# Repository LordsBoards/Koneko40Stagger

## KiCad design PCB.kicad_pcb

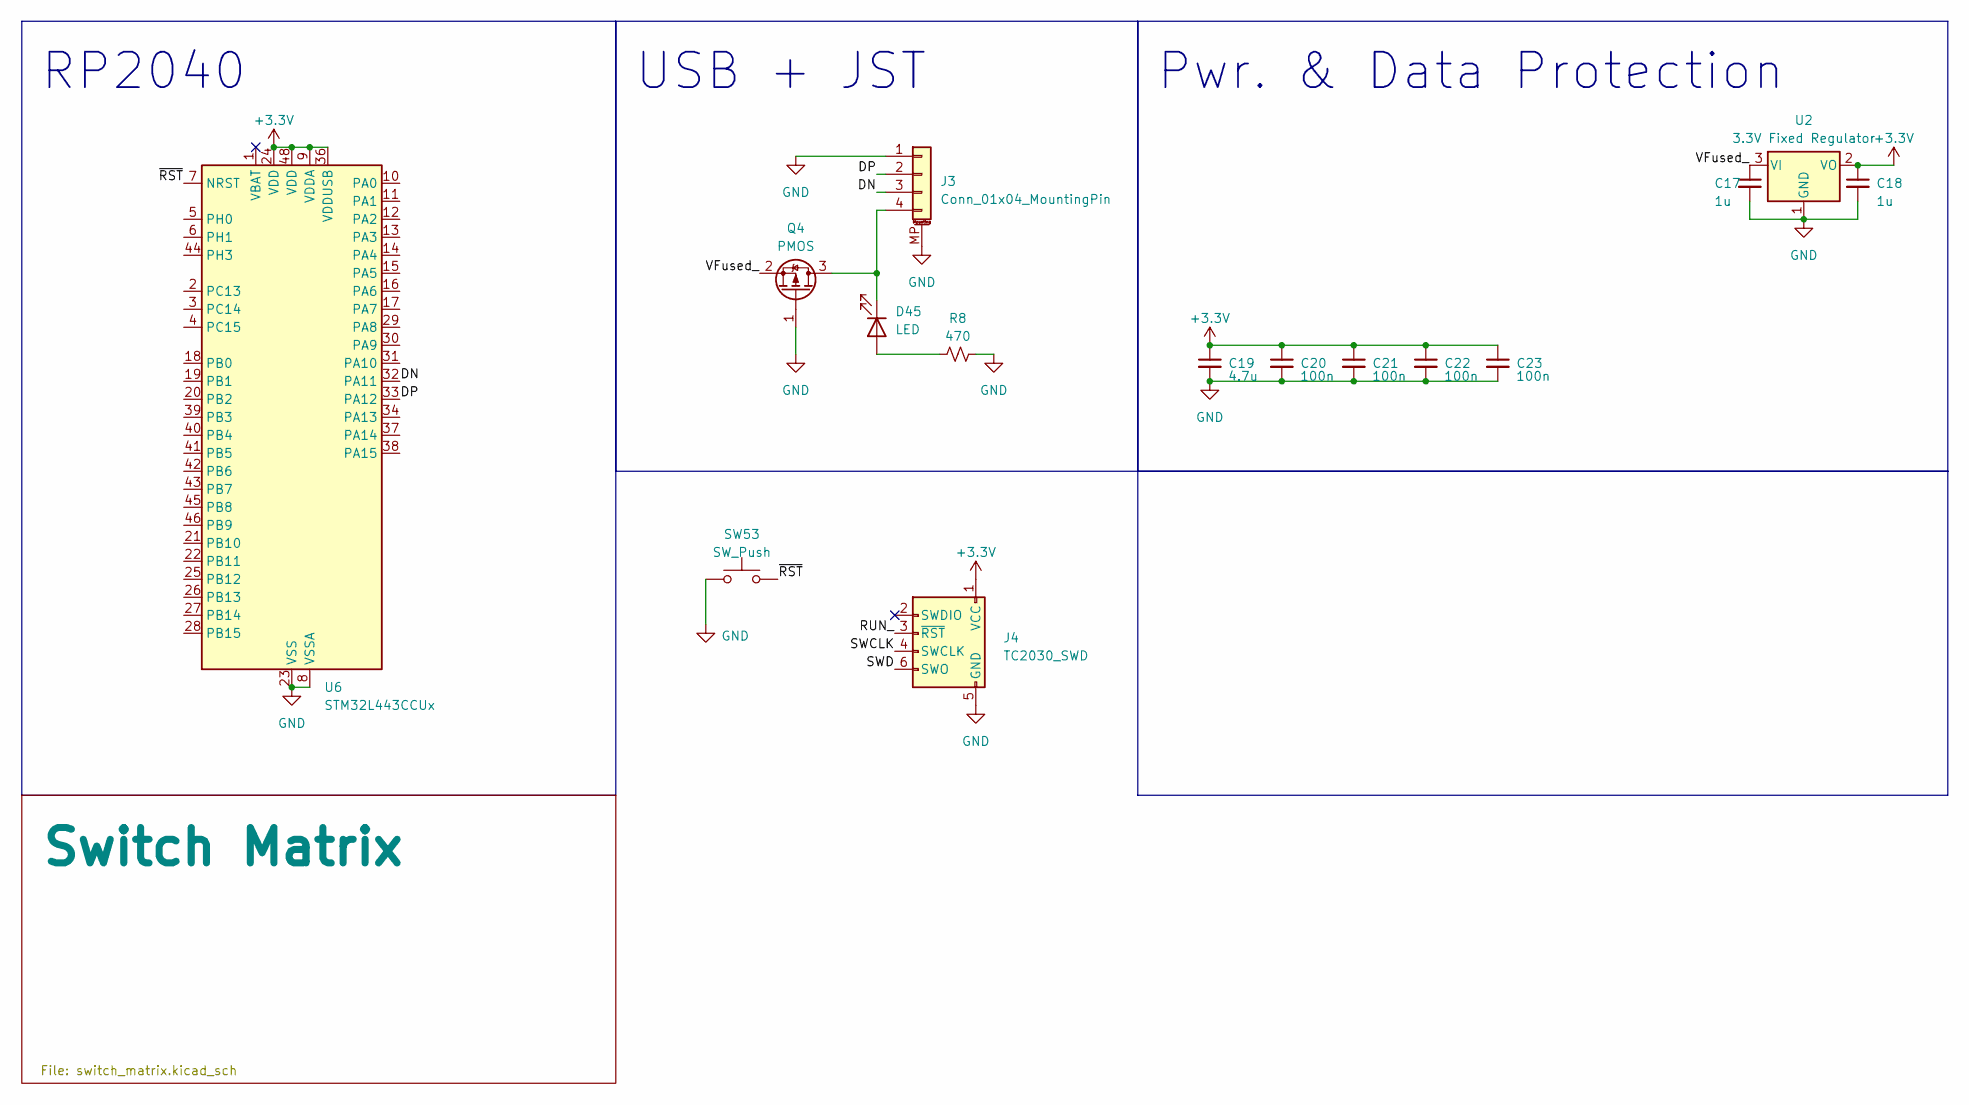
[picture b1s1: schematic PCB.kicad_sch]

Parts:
C17, C18: 1u; C_0402_1005Metric; LCSC C52923
C19: 4.7u; C_0402_1005Metric; LCSC C52923
C20, C21, C22, C23: 100n; C_0402_1005Metric; LCSC C1525
D45: LED; R_0603_1608Metric; LCSC C2286
J3: Conn_01x04_MountingPin; Molex_Pico-EZmate_78171-0004_1x04-1MP_P1.20mm_Vertical; LCSC C528030
J4: TC2030_SWD; CON_TC2030_outlined
Q4: PMOS; SOT-323_SC-70; LCSC C99272
R8: 470; R_0603_1608Metric; LCSC C23179
SW53: SW_Push; SW_SPST_SKQG_WithoutStem; LCSC C115351
U2: 3.3V Fixed Regulator; TSOT-23; LCSC C150715
U6: STM32L443CCUx; QFN-48-1EP_7x7mm_P0.5mm_EP5.6x5.6mm

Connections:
+3.3V: C18.1, C19.1, C20.1, C21.1, C22.1, C23.1, J4.1 (VCC), U2.2 (VO), U6.9 (VDDA), U6.24 (VDD), U6.36 (VDDUSB), U6.48 (VDD); also elsewhere on the board
/DN: J3.3, U6.32 (PA11); also elsewhere on the board
/DP: J3.2, U6.33 (PA12); also elsewhere on the board
/RUN_: J4.3 (~RST)
/SWCLK: J4.4 (SWCLK)
/SWD: J4.6 (SWO)
/VFused_: C17.1, Q4.2 (S), U2.3 (VI)
/~RST: SW53.2, U6.7 (NRST)
GND: C17.2, C18.2, C19.2, C20.2, C21.2, C22.2, C23.2, J3.1, J3.MP (MountPin), J4.5 (GND), Q4.1 (G), R8.1, SW53.1, U2.1 (GND), U6.8 (VSSA), U6.23 (VSS), U6.35 (VSS), U6.47 (VSS), U6.49 (VSS); also elsewhere on the board
unnamed: D45.2 (A), R8.2
unnamed 69: D45.1 (K), J3.4, Q4.3 (D); also elsewhere on the board

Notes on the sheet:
USB + JST
RP2040
Pwr. & Data Protection

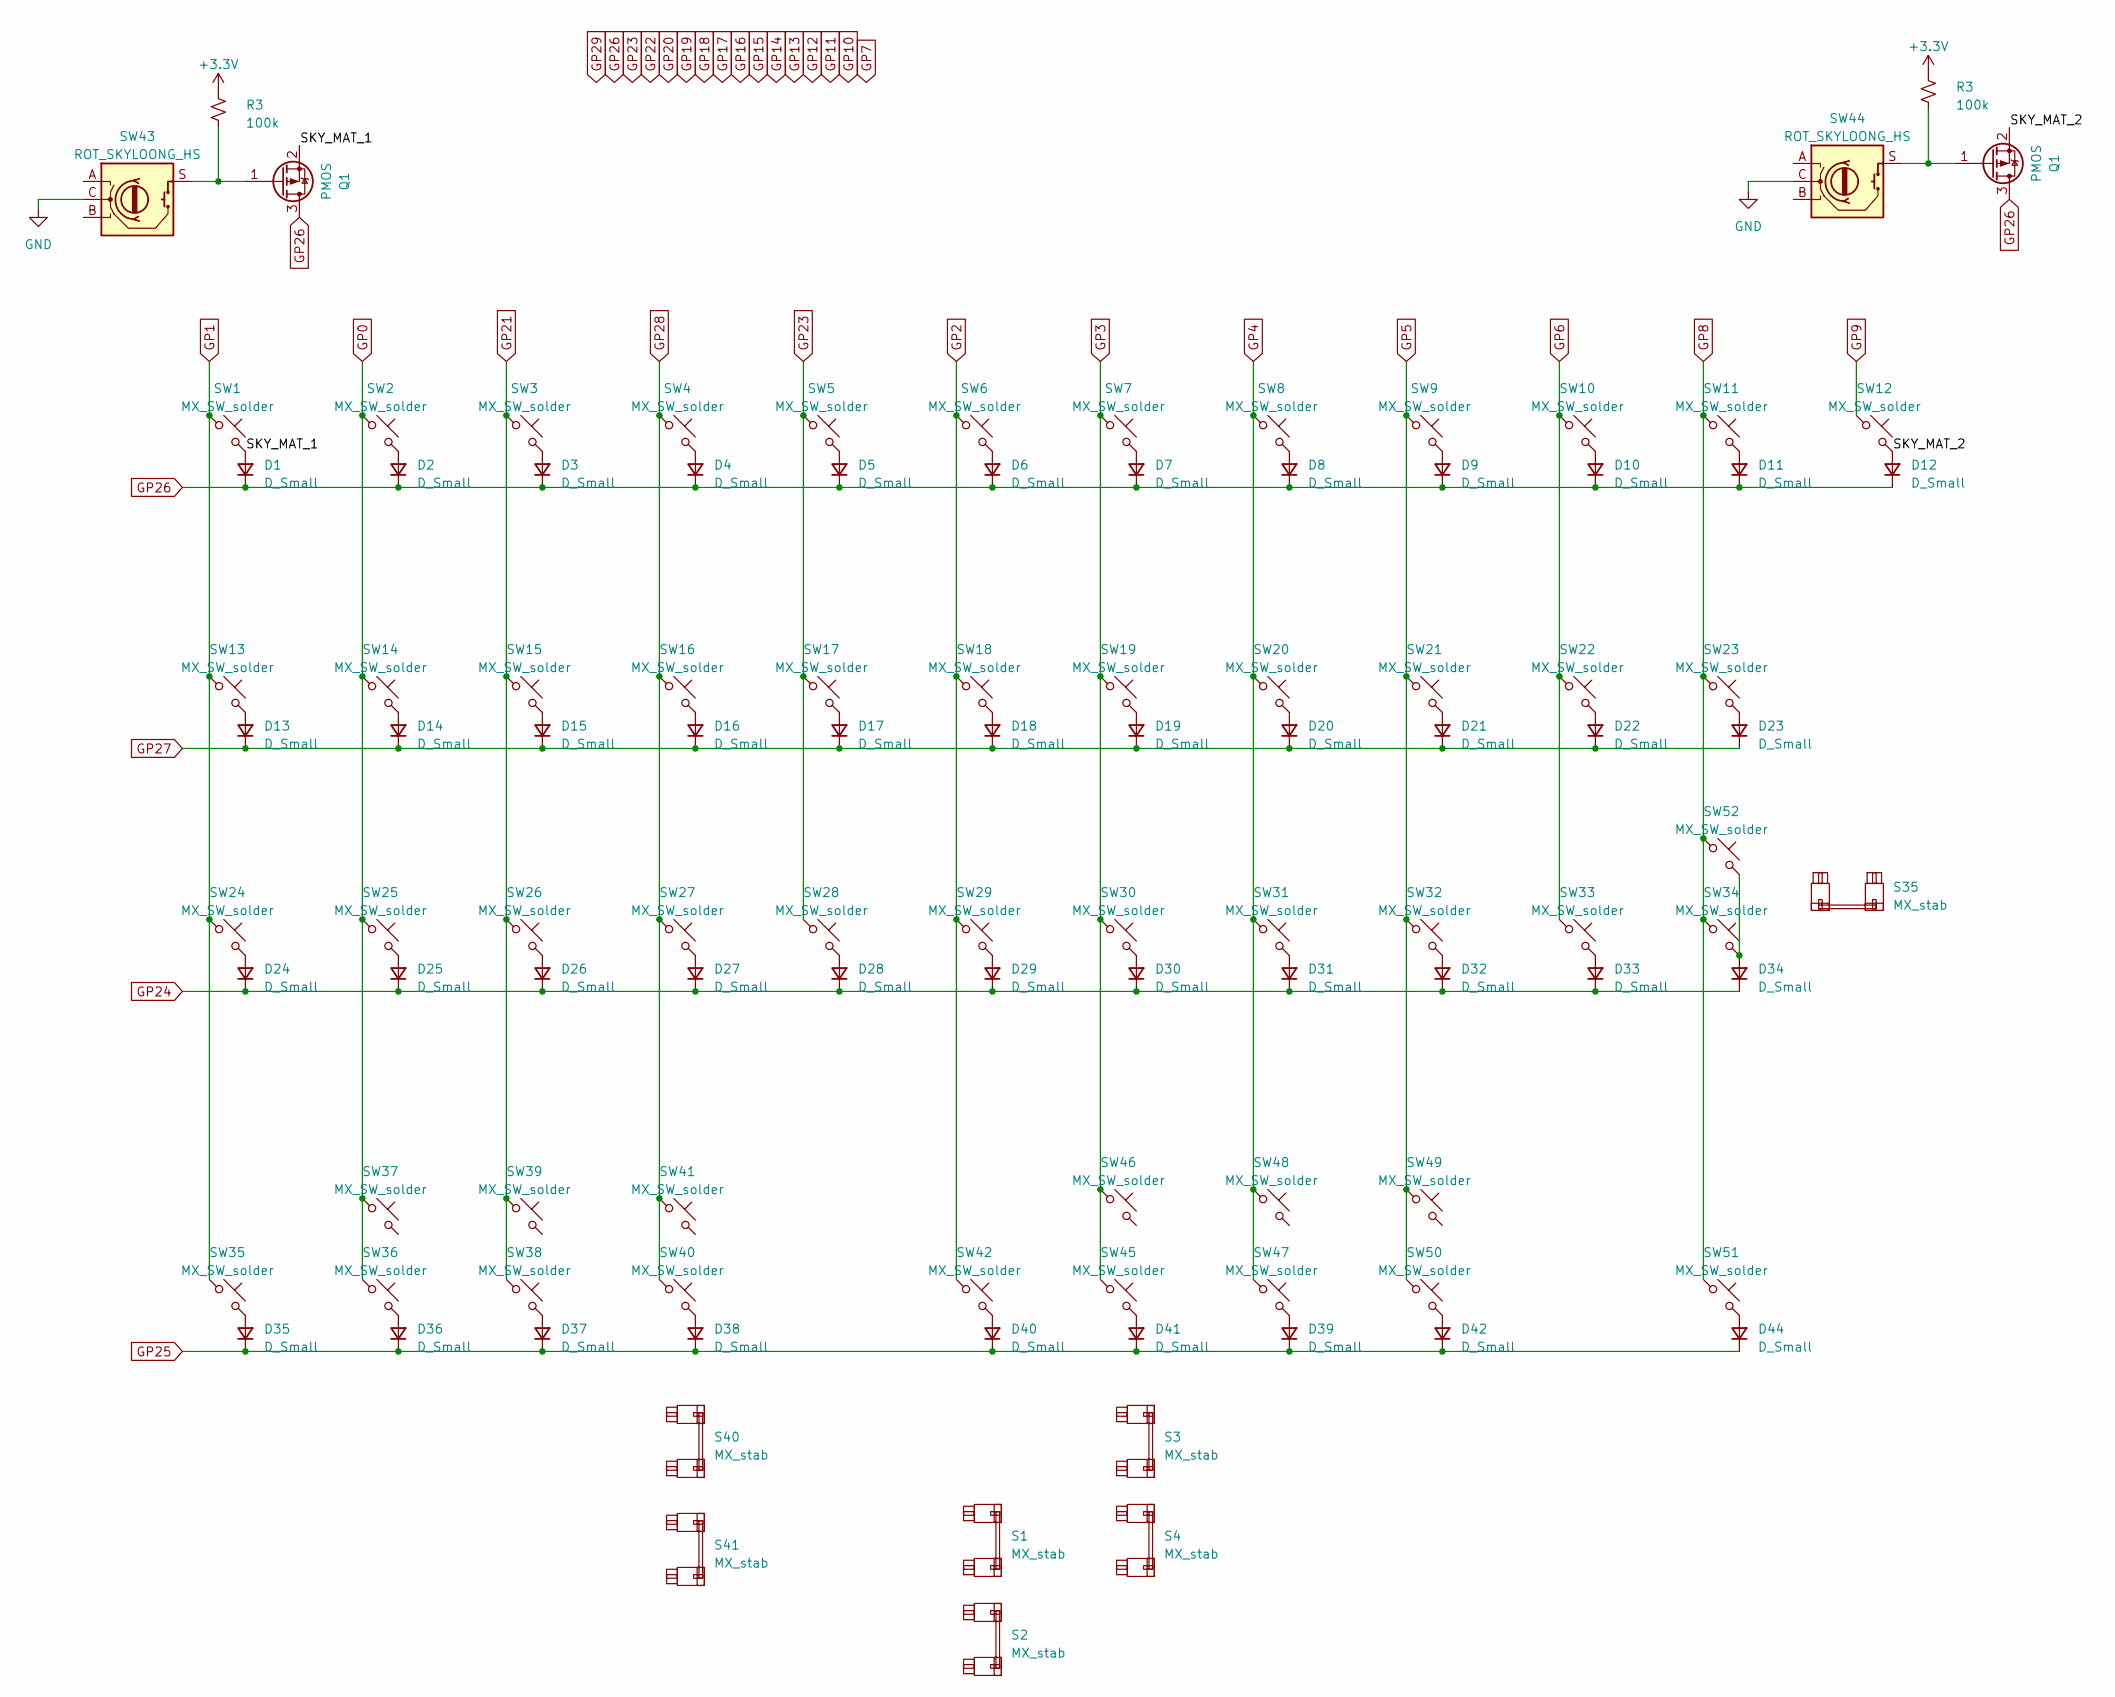
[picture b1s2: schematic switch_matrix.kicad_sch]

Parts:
D1, D2, D3, D4, D5, D6, D7, D8, D9, D10, D11, D12, D13, D14, D15, D16, D17, D18, D19, D20, D21, D22, D23, D24, D25, D26, D27, D28, D29, D30, D31, D32, D33, D34, D35, D36, D37, D38, D39, D40, D41, D42, D44: D_Small; D_SOD-123; LCSC C81598
Q1: PMOS; SOT-323_SC-70; LCSC C99272
R3: 100k; R_0402_1005Metric; LCSC C106234
S1: MX_stab; STAB_MX_P_7u
S2: MX_stab; STAB_MX_P_10u
S3, S40: MX_stab; STAB_MX_P_3u
S4, S35: MX_stab; STAB_MX_P_2.25u
S41: MX_stab; STAB_MX_P_2.75u
SW1, SW2, SW3, SW4, SW5, SW6, SW7, SW8, SW9, SW10, SW11, SW12, SW14, SW15, SW16, SW17, SW18, SW19, SW20, SW21, SW22, SW25, SW26, SW27, SW28, SW29, SW30, SW31, SW32, SW33, SW35, SW36, SW38, SW39, SW40, SW41, SW42, SW45, SW46, SW47, SW48, SW50, SW51, SW52: MX_SW_solder; SW_MX_1u
SW13, SW34: MX_SW_solder; SW_MX_1.25u
SW23, SW24: MX_SW_solder; SW_MX_1.75u
SW37, SW49: MX_SW_solder; SW_MX_1.5u
SW43, SW44: ROT_SKYLOONG_HS; ROT_SKYLOONG_HS-Switch

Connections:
/Switch Matrix/SKY_MAT_1: D1.2 (A), SW1.2; also elsewhere on the board
/Switch Matrix/SKY_MAT_2: D12.2 (A), SW12.2; also elsewhere on the board
GND: SW43.C, SW44.C; also elsewhere on the board
GP0: SW2.1, SW14.1, SW25.1, SW36.1, SW37.1
GP1: SW1.1, SW13.1, SW24.1, SW35.1
GP2: SW6.1, SW18.1, SW29.1, SW42.1
GP3: SW7.1, SW19.1, SW30.1, SW45.1, SW46.1
GP4: SW8.1, SW20.1, SW31.1, SW47.1, SW48.1
GP5: SW9.1, SW21.1, SW32.1, SW49.1, SW50.1
GP6: SW10.1, SW22.1, SW33.1
GP8: SW11.1, SW23.1, SW34.1, SW51.1, SW52.1
GP9: SW12.1
GP21: SW3.1, SW15.1, SW26.1, SW38.1, SW39.1
GP23: SW5.1, SW17.1, SW28.1
GP24: D24.1 (K), D25.1 (K), D26.1 (K), D27.1 (K), D28.1 (K), D29.1 (K), D30.1 (K), D31.1 (K), D32.1 (K), D33.1 (K), D34.1 (K)
GP25: D35.1 (K), D36.1 (K), D37.1 (K), D38.1 (K), D39.1 (K), D40.1 (K), D41.1 (K), D42.1 (K), D44.1 (K)
GP26: D1.1 (K), D2.1 (K), D3.1 (K), D4.1 (K), D5.1 (K), D6.1 (K), D7.1 (K), D8.1 (K), D9.1 (K), D10.1 (K), D11.1 (K), D12.1 (K); also elsewhere on the board
GP27: D13.1 (K), D14.1 (K), D15.1 (K), D16.1 (K), D17.1 (K), D18.1 (K), D19.1 (K), D20.1 (K), D21.1 (K), D22.1 (K), D23.1 (K)
GP28: SW4.1, SW16.1, SW27.1, SW40.1, SW41.1
unnamed: D2.2 (A), SW2.2
unnamed: D3.2 (A), SW3.2
unnamed: D4.2 (A), SW4.2
unnamed: D5.2 (A), SW5.2
unnamed: D6.2 (A), SW6.2
unnamed: D7.2 (A), SW7.2
unnamed: D8.2 (A), SW8.2
unnamed: D9.2 (A), SW9.2
unnamed: D10.2 (A), SW10.2
unnamed: D11.2 (A), SW11.2
unnamed: D13.2 (A), SW13.2
unnamed: D14.2 (A), SW14.2
unnamed: D15.2 (A), SW15.2
unnamed: D16.2 (A), SW16.2
unnamed: D17.2 (A), SW17.2
unnamed: D18.2 (A), SW18.2
unnamed: D19.2 (A), SW19.2
unnamed: D20.2 (A), SW20.2
unnamed: D21.2 (A), SW21.2
unnamed: D22.2 (A), SW22.2
unnamed: D23.2 (A), SW23.2
unnamed: D24.2 (A), SW24.2
unnamed: D25.2 (A), SW25.2
unnamed: D26.2 (A), SW26.2
unnamed: D27.2 (A), SW27.2
unnamed: D28.2 (A), SW28.2
unnamed: D29.2 (A), SW29.2
unnamed: D30.2 (A), SW30.2
unnamed: D31.2 (A), SW31.2
unnamed: D32.2 (A), SW32.2
unnamed: D33.2 (A), SW33.2
unnamed: D34.2 (A), SW34.2, SW52.2
unnamed: D35.2 (A), SW35.2
unnamed: D36.2 (A), SW36.2
unnamed: D37.2 (A), SW38.2
unnamed: D38.2 (A), SW40.2
unnamed: D39.2 (A), SW47.2
unnamed: D40.2 (A), SW42.2
unnamed: D41.2 (A), SW45.2
unnamed: D42.2 (A), SW50.2
unnamed: D44.2 (A), SW51.2
unnamed 70: SW44.S; also elsewhere on the board
unnamed 71: SW43.S; also elsewhere on the board

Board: 4 copper layers, 121 parts (62 on the bottom side), 68 nets, no tracks yet.

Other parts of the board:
J1: Conn_01x04_MountingPin; Molex_Pico-EZmate_78171-0004_1x04-1MP_P1.20mm_Vertical
Q2, Q3: PMOS; SOT-323_SC-70
R5, R6: 100k; R_0402_1005Metric

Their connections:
+3.3V: R5.2, R6.2; also elsewhere on the board
/DN: J1.3; also elsewhere on the board
/DP: J1.2; also elsewhere on the board
/Switch Matrix/SKY_MAT_1: Q3.2 (S); also elsewhere on the board
/Switch Matrix/SKY_MAT_2: Q2.2 (S); also elsewhere on the board
GND: J1.1, J1.MP (MountPin); also elsewhere on the board
GP26: Q2.3 (D), Q3.3 (D); also elsewhere on the board
unnamed 69: J1.4; also elsewhere on the board
unnamed 70: Q2.1 (G), R6.1; also elsewhere on the board
unnamed 71: Q3.1 (G), R5.1; also elsewhere on the board

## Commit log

2023-07-15 Layout complete
2023-08-06 Stagger
2023-08-20 Aug202023-7:30pm
2023-10-20 Refactored to use RP2040
2023-11-01 Fixed resistor part number.
